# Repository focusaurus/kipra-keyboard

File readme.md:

# kipra: It's kinda pragmatic.

A split ergonomic mechanical keyboard built with ergogen, kicad, and freecad.

There's a [blog post with details on this build](https://peterlyons.com/problog/2024/05/kipra-keyboard/) on my blog.

## What's in this repository

- The ergogen file at `v1/kipra-v1.ergogen.yaml`
- FreeCAD files for the case, palm rest, and various jigs and smaller parts
- The kicad PCB project files which were generated initially with ergogen then edited in kicad to route the tracks, add silkscreen, etc.
- Some reference pinout images for the RP2040 MCU I used
- a few screenshots from along the way
- a zip of the gerber files I sent to PCBWay if you just want to order PCBs

# Notes to self

## How to make the test print

- use ergogen via `./bin/build.sh` to output `v1/build/outlines/test_print.dxf`
- In freecad, start a new file and use Draft workbench
- Import the .dxf file. It will create many shapes.
- Select them all and hit the blue up arrow to upgrade them to wires
- Select them all and click the squiggly icon to convert to sketch
- Switch to Part Design Workbench
- Make a new body
- put the sketch in the body
- select the sketch and pad up 6mm

# MCU pinout on RP2040 (compatible)

| Pin | Use   | (center) | Use        | Pin |
| --- | ----- | -------- | ---------- | --- |
|     |       |          | Col Thumb  | P19 |
|     |       |          | col inner  | P18 |
| P6  | row 4 |          | col index  | P15 |
| P7  | row 3 |          | col middle | P15 |
| P8  | row 2 |          | col ring   | P16 |
| P9  | row 1 |          | col pinky  | P10 |

# v1 Solder Jumpers

TL;DR this is very confusing because reversible/symmetric PCBs are confusing.

With your PCBs laid out left & right as they will be when the keyboard is built and in use - top side facing up, you solder **ALL 4 COLUMNS OF JUMPERS ON THE PCB TOP SIDES**. None of the jumpers on the bottom side of the PCBs get soldered.

The left and right PCBs are symmetric, but the left and right MCUs are NOT. So to account for that we have do factor that into our pinouts and jumper routing.

Info for reference:

- In kipra v1, the footprint used was: [nice_nano.js from commit 753a](https://github.com/ceoloide/ergogen-footprints/blob/753a3464b552da21bd121a076ddfa4b47fadcfe8/nice_nano.js) in github.com/ceoloide/ergogen-footprints.
- This version did not yet support the `reverse_mount` parameter. If kipra v2 becomes a thing, we'll do that.
- However, the nice_nano footprint is design with the following configuration in mind (which we do NOT want to use in the kipra):
  - you want to mount your MCUs face down (Dunno, many folks like this?)
  - you want the jumper solders on the back so they are out of sight and don't obscure the silkscreen for the MCU pinout labels
- BUT in the case of the kipra v1, I specifically want to mount my MCUs face up because they have on-board reset buttons so flashing them is easy and I don't need a reset button on the main keyboard PCB. I added support for one just in case anyway, but hope to not have to use it. In general, I want to support the trend of the hobbyist MCUs having conveniences built-in so the barrier to build a custom keyboard is lower, and every little bit helps.

## How to: model the case in FreeCad

- start a new file
- switch to the Draft workbench
- import `v1/build/outlines/plate-shape.dxf`
- select all the shapes in the tree view
- click "Upgrade" blue up arrow to get a wire
- click the wire and click the squiggly "convert birectionally from draft to sketch"
- switch to the Part workbench
- select the sketch and select the 2D offset (hidden behind an arrow next to 3D offset)
- set distance to 2.6mm (2.4 for the wall and 0.2 for fit)
  - set the join type to tangent!
- click fill offset
- select the 2D offset in the tree view and click extrude to 10mm

## How to: model the case in FreeCAD (prototype 6)
- start a new file
- switch to the Draft workbench
- import `v1/build/outlines/plate-shape.dxf`
- select all the shapes in the tree view
- click "Upgrade" blue up arrow to get a wire
- click "Upgrade" blue up arrow again to get a face
- Use the offset 2D tool to get an offset 2.4mm from the edge of the face
  - set the join type to tangent!
- extrude that offset up 12mm and click to make a solid
- click the wire and click the squiggly "convert birectionally from draft to sketch"
  - this gives us the outer wall
- extrude the face for the bottow up 2mm
- this is all not exactly right but I was experimenting too quickly to keep track of it

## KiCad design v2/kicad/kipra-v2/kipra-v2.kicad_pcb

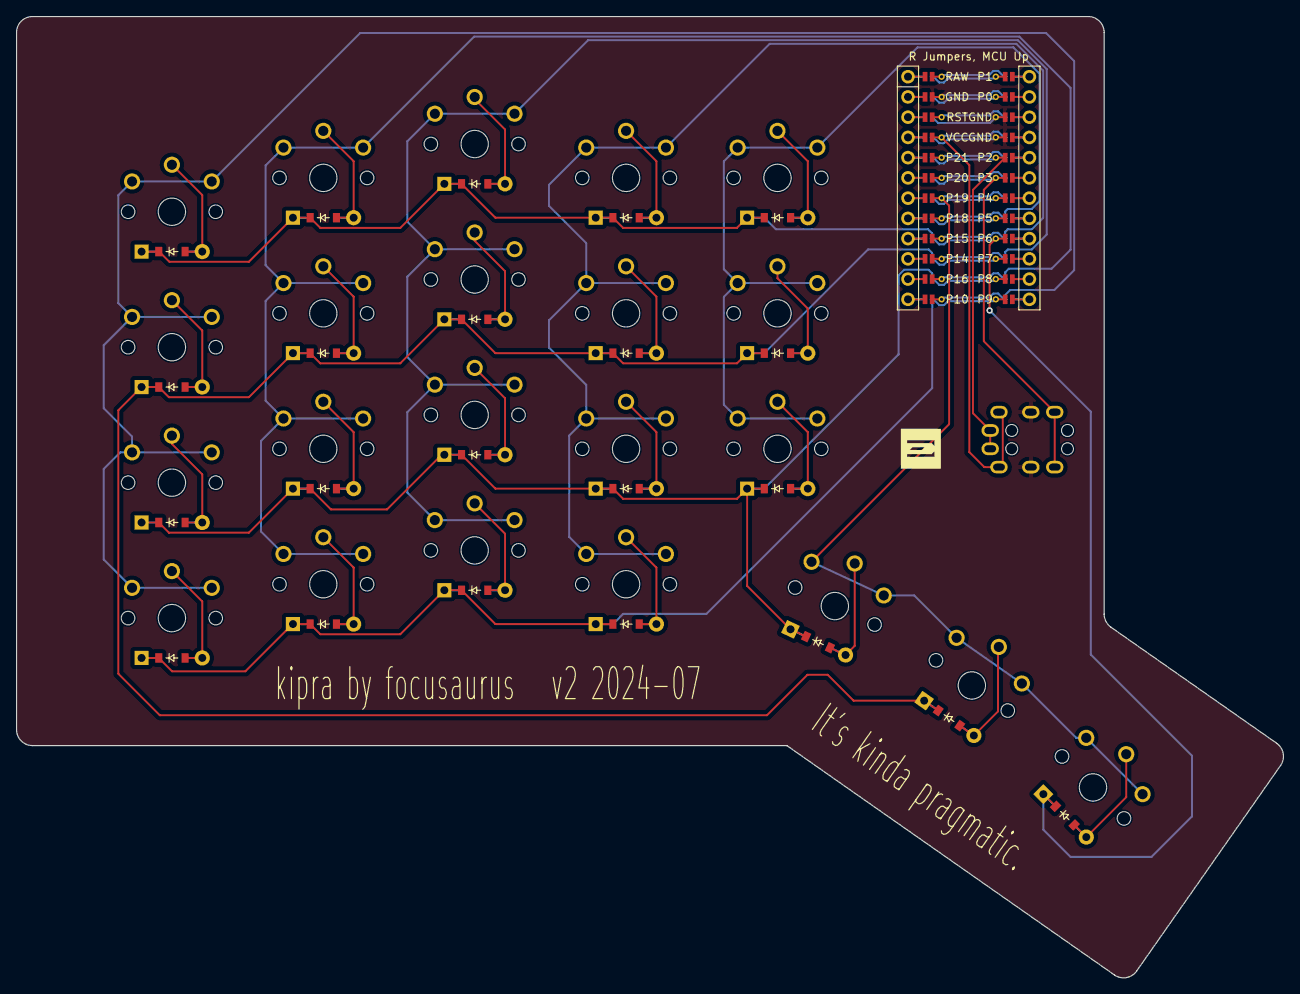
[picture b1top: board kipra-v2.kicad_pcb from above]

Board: 2 copper layers, 159.0 x 120.6 mm, 47 parts (0 on the bottom side), 48 nets.

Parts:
D1, D2, D3, D4, D5, D6, D7, D8, D9, D10, D11, D12, D13, D14, D15, D16, D17, D18, D19, D20, D21, D22: ComboDiode
LOGO1: utility_ergogen_logo
MCU1: mcu_nice_nano
S1, S2, S3, S4, S5, S6, S7, S8, S9, S10, S11, S12, S13, S14, S15, S16, S17, S18, S19, S20, S21, S22: PG1350
TRRS1: TRRS-PJ-320A-dual

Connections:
GND: MCU1.103, MCU1.104, MCU1.123, TRRS1.3
MCU1_1: MCU1.1, MCU1.24
MCU1_2: MCU1.2, MCU1.23
MCU1_3: MCU1.3, MCU1.22
MCU1_4: MCU1.4, MCU1.21
MCU1_5: MCU1.5, MCU1.20
MCU1_6: MCU1.6, MCU1.19
MCU1_7: MCU1.7, MCU1.18
MCU1_8: MCU1.8, MCU1.17
MCU1_9: MCU1.9, MCU1.16
MCU1_10: MCU1.10, MCU1.15
MCU1_11: MCU1.11, MCU1.14
MCU1_12: MCU1.12, MCU1.13
P2: MCU1.105, TRRS1.1
P3: MCU1.106, TRRS1.4
P6: D4.1, D8.1, D12.1, D16.1, D19.1, D20.1, MCU1.109
P7: D3.1, D7.1, D11.1, D15.1, D18.1, D21.1, MCU1.110
P8: D2.1, D6.1, D10.1, D14.1, D17.1, D22.1, MCU1.111
P9: D1.1, D5.1, D9.1, D13.1, MCU1.112
P10: MCU1.113, S1.1, S2.1, S3.1, S4.1
P14: MCU1.115, S9.1, S10.1, S11.1, S12.1
P15: MCU1.116, S13.1, S14.1, S15.1, S16.1
P16: MCU1.114, S5.1, S6.1, S7.1, S8.1
P18: MCU1.117, S17.1, S18.1, S19.1
P19: MCU1.118, S20.1, S21.1, S22.1
VCC: MCU1.121, TRRS1.2
index_four: D16.2, S16.2
index_one: D13.2, S13.2
index_three: D15.2, S15.2
index_two: D14.2, S14.2
inner_four: D19.2, S19.2
inner_three: D18.2, S18.2
inner_two: D17.2, S17.2
middle_four: D12.2, S12.2
middle_one: D9.2, S9.2
middle_three: D11.2, S11.2
middle_two: D10.2, S10.2
pinky_four: D4.2, S4.2
pinky_one: D1.2, S1.2
pinky_three: D3.2, S3.2
pinky_two: D2.2, S2.2
ring_four: D8.2, S8.2
ring_one: D5.2, S5.2
ring_three: D7.2, S7.2
ring_two: D6.2, S6.2
thumb_far: D20.2, S20.2
thumb_middle: D21.2, S21.2
thumb_near: D22.2, S22.2

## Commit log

2023-05-26 working on ergogen PCB layout for kipra
2023-05-26 tweak thumb arc
2023-05-26 figured out default spread and padding
    - $default_spread and $default_padding go under the "units" property
    - got inner finger included in the main fingers zone and skip working
    for row four
2023-05-26 comments on default values
2023-05-26 tweak binds for cleaner outline
2023-08-18 ergogen update
2023-08-18 ergogen raw yaml snapshot
2023-08-18 FreeCAD files for fit test parts
2023-08-18 ignore files that can be regenerated from FreeCAD
2023-08-26 add diodes in ergogen
2023-08-26 re-add inner r4. Move trrs.
    About to flip flop thumb rows vs cols
2023-08-26 thumb 1 column 3 rows variant
2023-08-26 got thumb arc rotated correctly
2023-08-26 clean up thumb outline binds
2023-08-26 got outline integrated into pcb
2023-08-26 added reset button and fixed placement
2023-08-26 first attempt at key matrix net
2023-08-26 working on matrix nets
2023-08-26 mounting holes
    Need to reference a local mountinghole.js footprint in this project from ergogen now
2023-08-26 case bottom jscad
2023-08-26 remove extraneous yaml arrays
2023-12-17 build case with openscad
2023-12-17 Adjust thumb arc position for mods on bottom row
2023-12-18 Redefine thumb are as 1 col 3 rows
2023-12-18 Tweak outline binds
2023-12-18 tweak thumb binds and mounting hole offsets
2023-12-18 use nice_nano_pretty MCU footprint
2023-12-19 MCU has on-board reset
    Don't need a button footprint on the PCB
2024-01-24 Add outline for test print
    Thanks to hand_le in absolem club discord for the help
2024-01-26 Tweak thumb arc and pinky stagger based on test print
2024-01-30 Fix mounting holes and add one at end of thumb arc
2024-01-31 add choc footprint with traces
    Need to put this in ergogen branch
2024-01-31 docs
2024-01-31 Skip inner one and bring thumb arc closer
2024-01-31 thumb arc was possibly overlapping keycaps
    Space it out a bit more
2024-01-31 Space thumb arc out to avoid keycap collision
2024-02-25 use build dir instead of .build for convenience
2024-02-25 Readd index one and shift thumb cluster back down
2024-02-25 ignore build dir
2024-02-25 2024-02-25c move thumb arc higher
2024-02-25 Bring thumb arc more tuck and bind the bottom huge
2024-02-29 thumb arc position final-FINAL.pdf
2024-03-17 trace routes up pinky column
2024-03-17 route traces up ring column
2024-03-17 route traces up middle column
2024-03-17 I think maybe I just need ground now
2024-03-17 only DRC errors are GND filled zone issues
2024-03-17 all DRC errors fixed
2024-03-18 Fix net issue by removing leading zeros
    ceoloide on discord says this is why I'm missing some traces
2024-03-20 about to edit kicad pcb file by hand to fix row to mcu traces
2024-03-20 hand editing pcb file seems to have fixed the row to mcu traces
2024-03-23 ergogen move mounting hole out of crowded mcu interior
2024-03-23 DRC passes!
2024-03-24 add silkscreen text
2024-03-24 added a reset button (ergogen redo)
    Had to go back to ergogen. Will need to redo all the traces now.
2024-03-25 checkpoint before starting over to move row pins down one slot to the corner
2024-03-25 move row pins down to the corner
2024-03-25 pinout in readme
2024-03-26 cleaned up tracks. no DRC errors.
    Paired with Jesse and Charles from Recurse Center
2024-03-27 added silkscreen text
2024-03-30 Add silkscreen texts as separate file
2024-03-30 Updated version from RC pairing with Jesse
2024-03-30 Tweak row nets and bind +2mm for room next to MCU
2024-03-30 DRC passes
2024-03-30 kicad done should be ready to go
2024-04-03 vial progress
2024-04-15 v1 kicad pcb
2024-04-15 gerber files sent to pcbway
2024-04-15 vial support improvements
2024-04-15 photo of MCU face and jumper pad solder instructions
2024-04-21 add correct pinout/footprint image from vendor
2024-05-14 readme updates on case modeling
2024-05-14 kicad
2024-05-14 major cleanup and reorg of repo filesystem layout
    - kicad and ergogen builds might be broken by this
2024-05-14 tidy repo
2024-05-14 got ergogen cli build working again
2024-05-14 remove duplicate pinout image
2024-05-14 mark version 1.0.0 in the ergogen yaml file
2024-05-14 don't need npm package files since we're using npx now
2024-05-14 add image to readme
2024-05-14 move text silkscreens sinppet into kicad directory
2024-05-14 add gerber file that was sent to fabrication for the 2024-04 v1 build
2024-05-14 add gerber
2024-05-18 add bottom plate
    idea here is to use the mounting holes to bolt this to the PCB, then
    glue a shelf liner to this instead of directly to the hotswap sockets
2024-05-18 bottom plate first session
2024-05-18 much better way to make cases
    This will spit out .stl files for a 2-piece travel case.
    Bottom case should fit the PCB and walls are tall enough to just clear
    the keycaps.
    Top case then nests over top of that.
    No closure/lock mechanism yet.
2024-05-19 much nicer full travel case top
2024-05-26 Add travel case .stl generated files for ease
    These can be rebuilt with ergogen, but for folks who want to just
    download and print, adding them to github
2024-05-26 v2 start
    - less pinky stagger
    - move thumb arc closer to inner 2
    - outline closer to a rectangle
    - adjust binding accordingly
2024-05-26 v2 MCU and TRRS position tweaks
2024-05-27 no stagger on inner
    Want thumb arc further away
2024-05-27 last thumb arc keycap was colliding. Add more clearance.
2024-05-27 failed experiment with thumb arc beside inner2
2024-05-27 clean up binds
2024-05-27 smooth thumb arc bind fillet
    Bind the middle key big and near/far zero to get well-connected edge
    geometry
2024-05-27 fix MCU shift
    Want to make sure the USB connector doesn't poke out past the PCB edge
2024-05-29 thumb arc further in. Clean up units to remove explicit multiplication.
2024-06-23 increase bind base to 7 for more room for bottom plate
    For some reason ergogen starts throwing an error if bind base is 8
2024-06-29 wider binding to make room for bottom plate
2024-06-30 dialed in text and wider binding for bottom plate
2024-06-30 thinner bottom plate to just clear the diodes
2024-06-30 move ergogen logo near TRRS
2024-07-07 ceoloide/ergogen-footprints we are using in kipra v2
    These came from github.com/ceoloide/ergogen-footprints
    main branch commit
    commit feb194fbc753aca7074028fcc73a2d617b5975f8 (HEAD -> main,
    origin/main, origin/HEAD)
    Author: Marco Massarelli <marco.massarelli@gmail.com>
    Date: Thu May 23 09:49:54 2024 -0400
2024-07-07 kipra PCB preview image from KiCAD
2024-07-07 traces: false on choc footprint seems better
2024-07-07 all tracks routed and passing DRC in kicad
2024-07-07 tidy tracks so all F.cu go up interior of MCU
2024-08-05 gerbers dir
2024-08-05 move case top finger pull
    It was hitting the corner
